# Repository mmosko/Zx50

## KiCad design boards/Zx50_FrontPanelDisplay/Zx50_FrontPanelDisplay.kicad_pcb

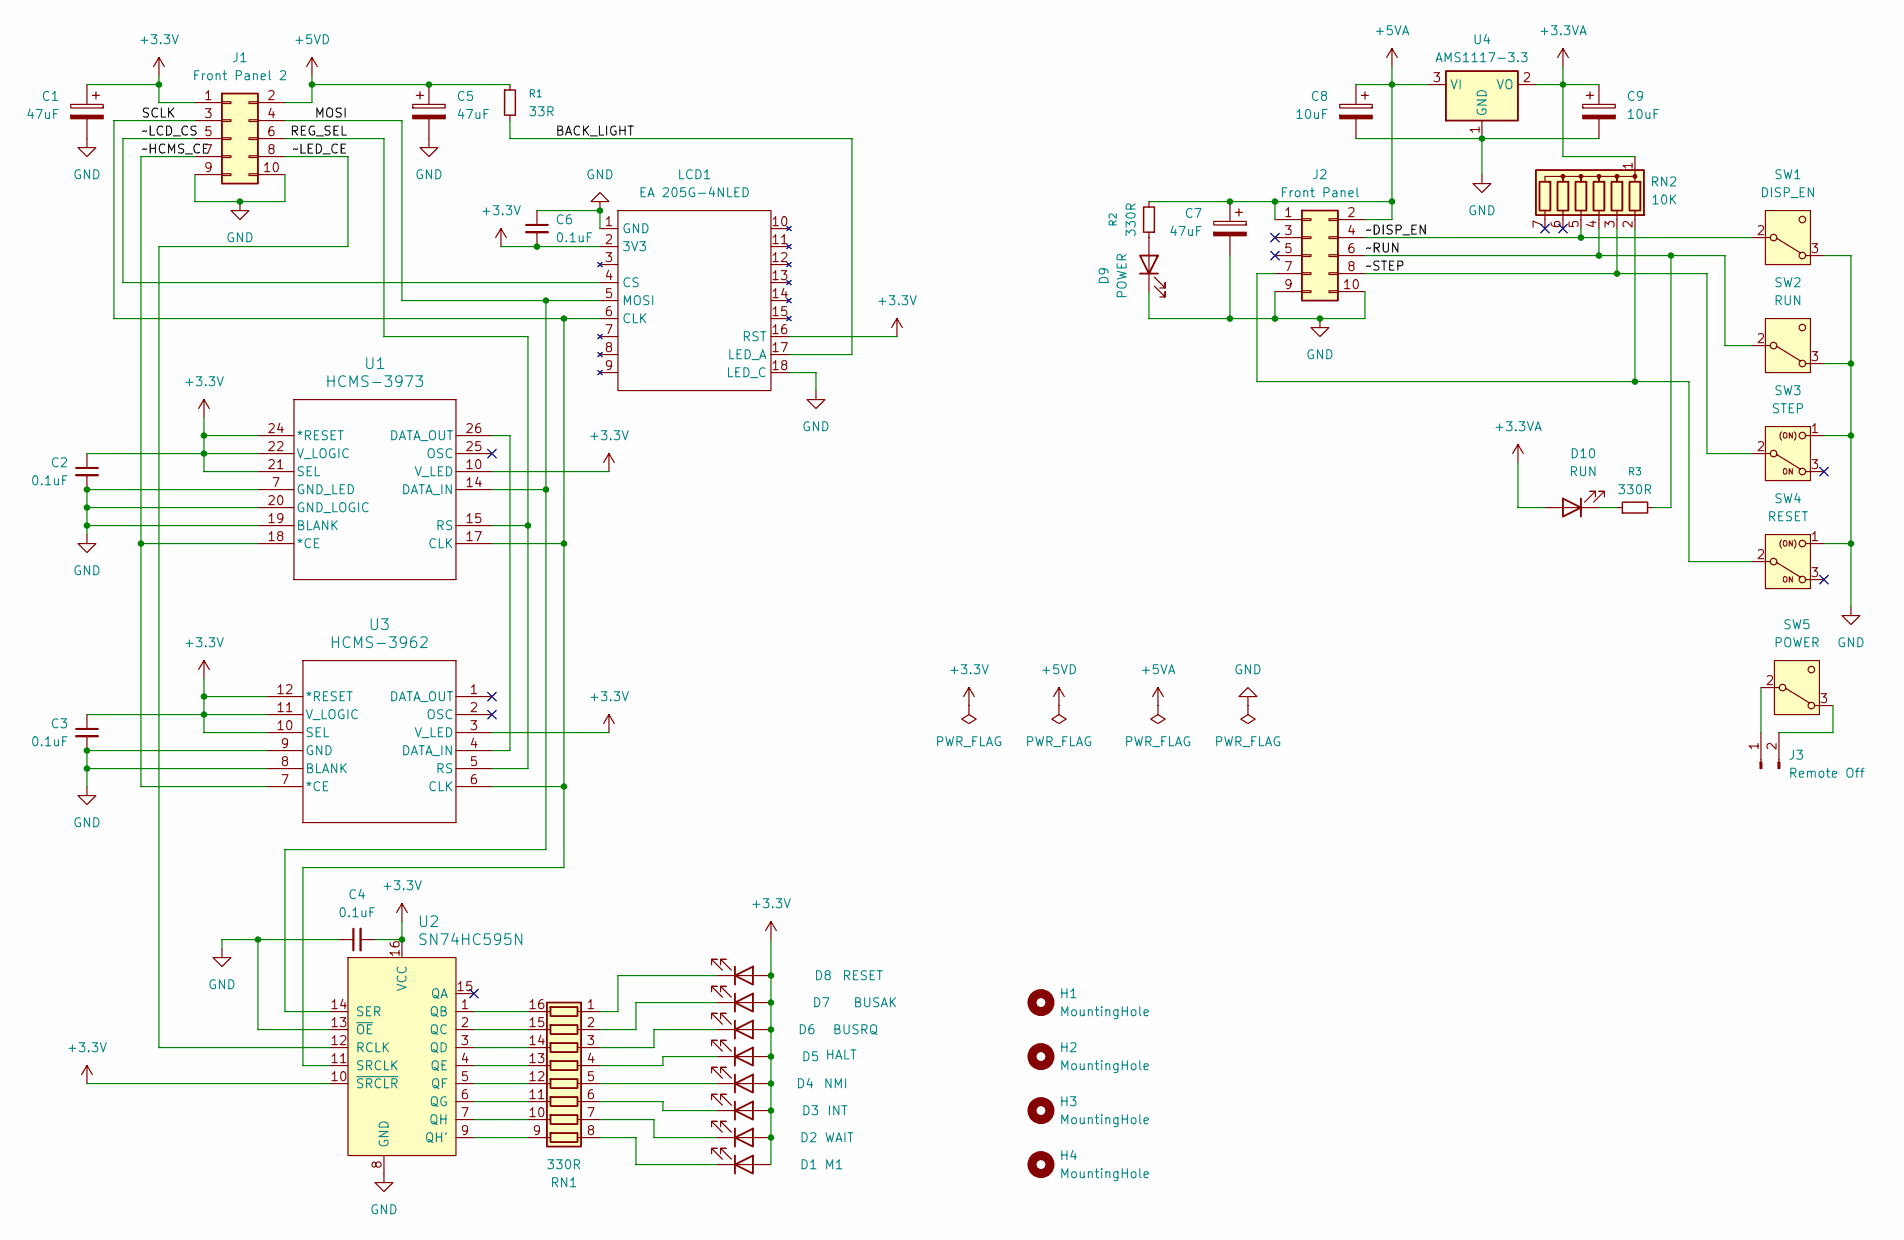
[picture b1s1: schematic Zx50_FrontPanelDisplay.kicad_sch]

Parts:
C1, C5, C7: 47uF; CP_Radial_D5.0mm_P2.00mm
C2, C3, C4, C6: 0.1uF; C_Disc_D5.0mm_W2.5mm_P5.00mm; DigiKey_PN BC1101CT-ND
C8, C9: 10uF; CP_Radial_Tantal_D5.0mm_P2.50mm; Mouser_PN 80-T350E106K025; DigiKey_PN 399-1418-ND
D1: M1; LED_D3.0mm
D2: WAIT; LED_D3.0mm
D3: INT; LED_D3.0mm
D4: NMI; LED_D3.0mm
D5: HALT; LED_D3.0mm
D6: BUSRQ; LED_D3.0mm
D7: BUSAK; LED_D3.0mm
D8: RESET; LED_D3.0mm
D9: POWER; LED_D3.0mm
D10: RUN; LED_D3.0mm
H1, H2, H3, H4: MountingHole; MountingHole_3.2mm_M3
J1: Front Panel 2; IDC-Header_2x05_P2.54mm_Vertical_SMD; Mouser_PN 710-61231020621; DigiKey_PN 732-2098-ND
J2: Front Panel; IDC-Header_2x05_P2.54mm_Vertical_SMD; Mouser_PN 710-61231020621; DigiKey_PN 732-2098-ND
J3: Remote Off; PinHeader_1x02_P2.54mm_Vertical
LCD1: EA 205G-4NLED; EA_DIG205G-4NLED; Digi-Key_PN 1481-EADIP205G-4NLED-ND
R1: 33R; R_Axial_DIN0207_L6.3mm_D2.5mm_P7.62mm_Horizontal
R2, R3: 330R; R_Axial_DIN0207_L6.3mm_D2.5mm_P7.62mm_Horizontal
RN1: 330R; DIP-16_W7.62mm
RN2: 10K; R_Array_SIP7
SW1: DISP_EN; NKK_MN11_SPST_W03
SW2: RUN; NKK_MN11_SPST_W03
SW3: STEP; NKK_MN15_SPDT_W03
SW4: RESET; NKK_MN15_SPDT_W03
SW5: POWER; NKK_MN11_SPST_W03
U1: HCMS-3973; DIP12_HCMS-397X_BRA
U2: SN74HC595N; SOP-16_4.4x10.4mm_P1.27mm; MPN SN74HC595N; Digi-Key_PN 296-1600-5-ND
U3: HCMS-3962; DIP12_HCMS-396X_BRA
U4: AMS1117-3.3; SOT-223-3_TabPin2; Mouser_PN 926-LM1117MPX3.3NOPB

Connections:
+3.3V: C1.1, C2.1, C3.1, C4.2, C6.2, D1.2 (A), D2.2 (A), D3.2 (A), D4.2 (A), D5.2 (A), D6.2 (A), D7.2 (A), D8.2 (A), J1.1, LCD1.2 (3V3), LCD1.16 (RST), U1.10 (V_LED), U1.21 (SEL), U1.22 (V_LOGIC), U1.24 (*RESET), U2.10 (~SRCLR), U2.16 (VCC), U3.3 (V_LED), U3.10 (SEL), U3.11 (V_LOGIC), U3.12 (*RESET)
+3.3VA: C9.1, D10.2 (A), RN2.1 (common), U4.2 (VO)
+5VA: C7.1, C8.1, J2.1, J2.2, R2.2, U4.3 (VI)
+5VD: C5.1, J1.2, R1.1
/BACK_LIGHT: LCD1.17 (LED_A), R1.2
/MOSI: J1.4, LCD1.5 (MOSI), U1.14 (DATA_IN), U2.14 (SER)
/REG_SEL: J1.6, U1.15 (RS), U3.5 (RS)
/SCLK: J1.3, LCD1.6 (CLK), U1.17 (CLK), U2.11 (SRCLK), U3.6 (CLK)
/~DISP_EN: J2.4, RN2.5 (R4), SW1.2 (B)
/~HCMS_CE: J1.7, U1.18 (*CE), U3.7 (*CE)
/~LCD_CS: J1.5, LCD1.4 (CS)
/~LED_CE: J1.8, U2.12 (RCLK)
/~RUN: J2.6, R3.2, RN2.4 (R3), SW2.2 (B)
/~STEP: J2.8, RN2.3 (R2), SW3.2 (B)
GND: C1.2, C2.2, C3.2, C4.1, C5.2, C6.1, C7.2, C8.2, C9.2, D9.1 (K), J1.9, J1.10, J2.9, J2.10, LCD1.1 (GND), LCD1.18 (LED_C), SW1.3 (C), SW2.3 (C), SW3.1 (A), SW4.1 (A), U1.7 (GND_LED), U1.19 (BLANK), U1.20 (GND_LOGIC), U2.8 (GND), U2.13 (~OE), U3.8 (BLANK), U3.9 (GND), U4.1 (GND)
unnamed: D1.1 (K), RN1.8 (R8.1)
unnamed: D2.1 (K), RN1.7 (R7.1)
unnamed: D3.1 (K), RN1.6 (R6.1)
unnamed: D4.1 (K), RN1.5 (R5.1)
unnamed: D5.1 (K), RN1.4 (R4.1)
unnamed: D6.1 (K), RN1.3 (R3.1)
unnamed: D7.1 (K), RN1.2 (R2.1)
unnamed: D8.1 (K), RN1.1 (R1.1)
unnamed: D9.2 (A), R2.1
unnamed: D10.1 (K), R3.1
unnamed: J2.7, RN2.2 (R1), SW4.2 (B)
unnamed: J3.1, SW5.2 (B)
unnamed: J3.2, SW5.3 (C)
unnamed: RN1.16 (R1.2), U2.1 (QB)
unnamed: RN1.15 (R2.2), U2.2 (QC)
unnamed: RN1.14 (R3.2), U2.3 (QD)
unnamed: RN1.13 (R4.2), U2.4 (QE)
unnamed: RN1.12 (R5.2), U2.5 (QF)
unnamed: RN1.11 (R6.2), U2.6 (QG)
unnamed: RN1.10 (R7.2), U2.7 (QH)
unnamed: RN1.9 (R8.2), U2.9 (QH')
unnamed: U1.26 (DATA_OUT), U3.4 (DATA_IN)

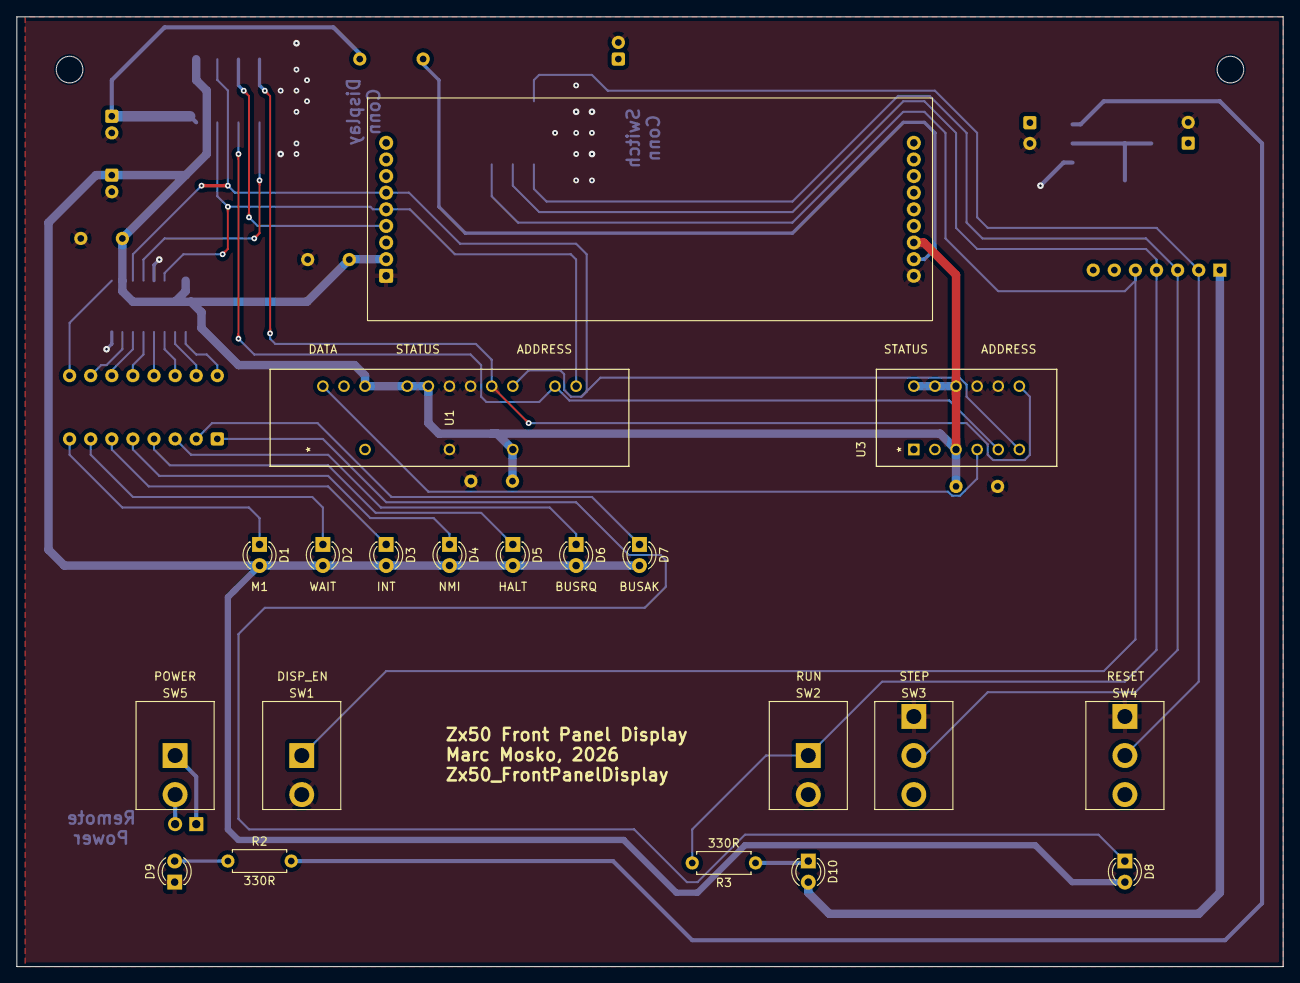
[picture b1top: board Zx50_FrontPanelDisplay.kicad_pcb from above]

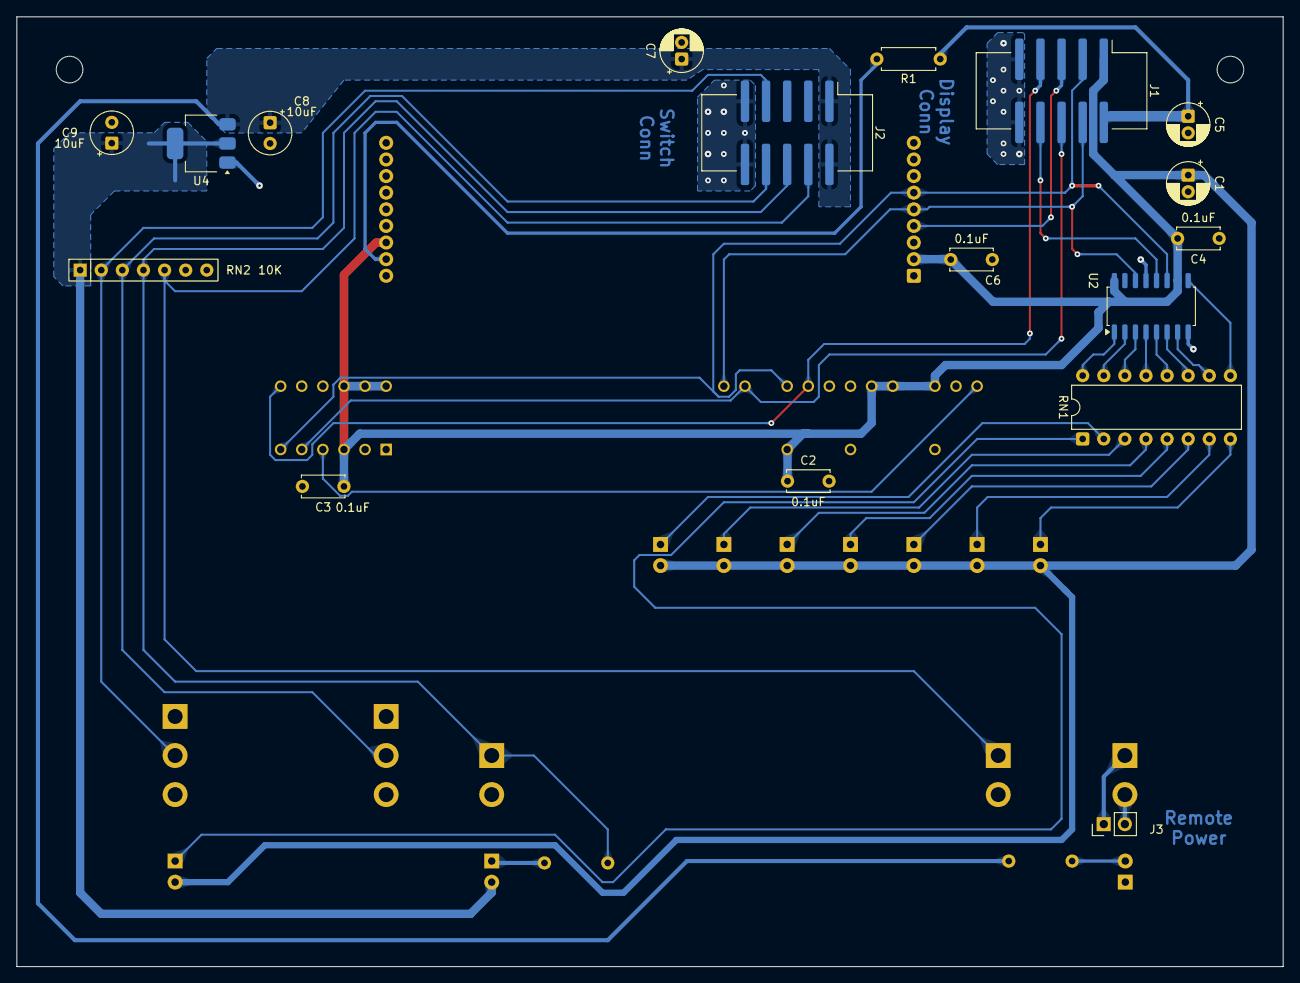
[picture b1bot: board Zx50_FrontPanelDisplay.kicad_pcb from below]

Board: 2 copper layers, 152.4 x 114.3 mm, 39 parts (17 on the bottom side), 37 nets.

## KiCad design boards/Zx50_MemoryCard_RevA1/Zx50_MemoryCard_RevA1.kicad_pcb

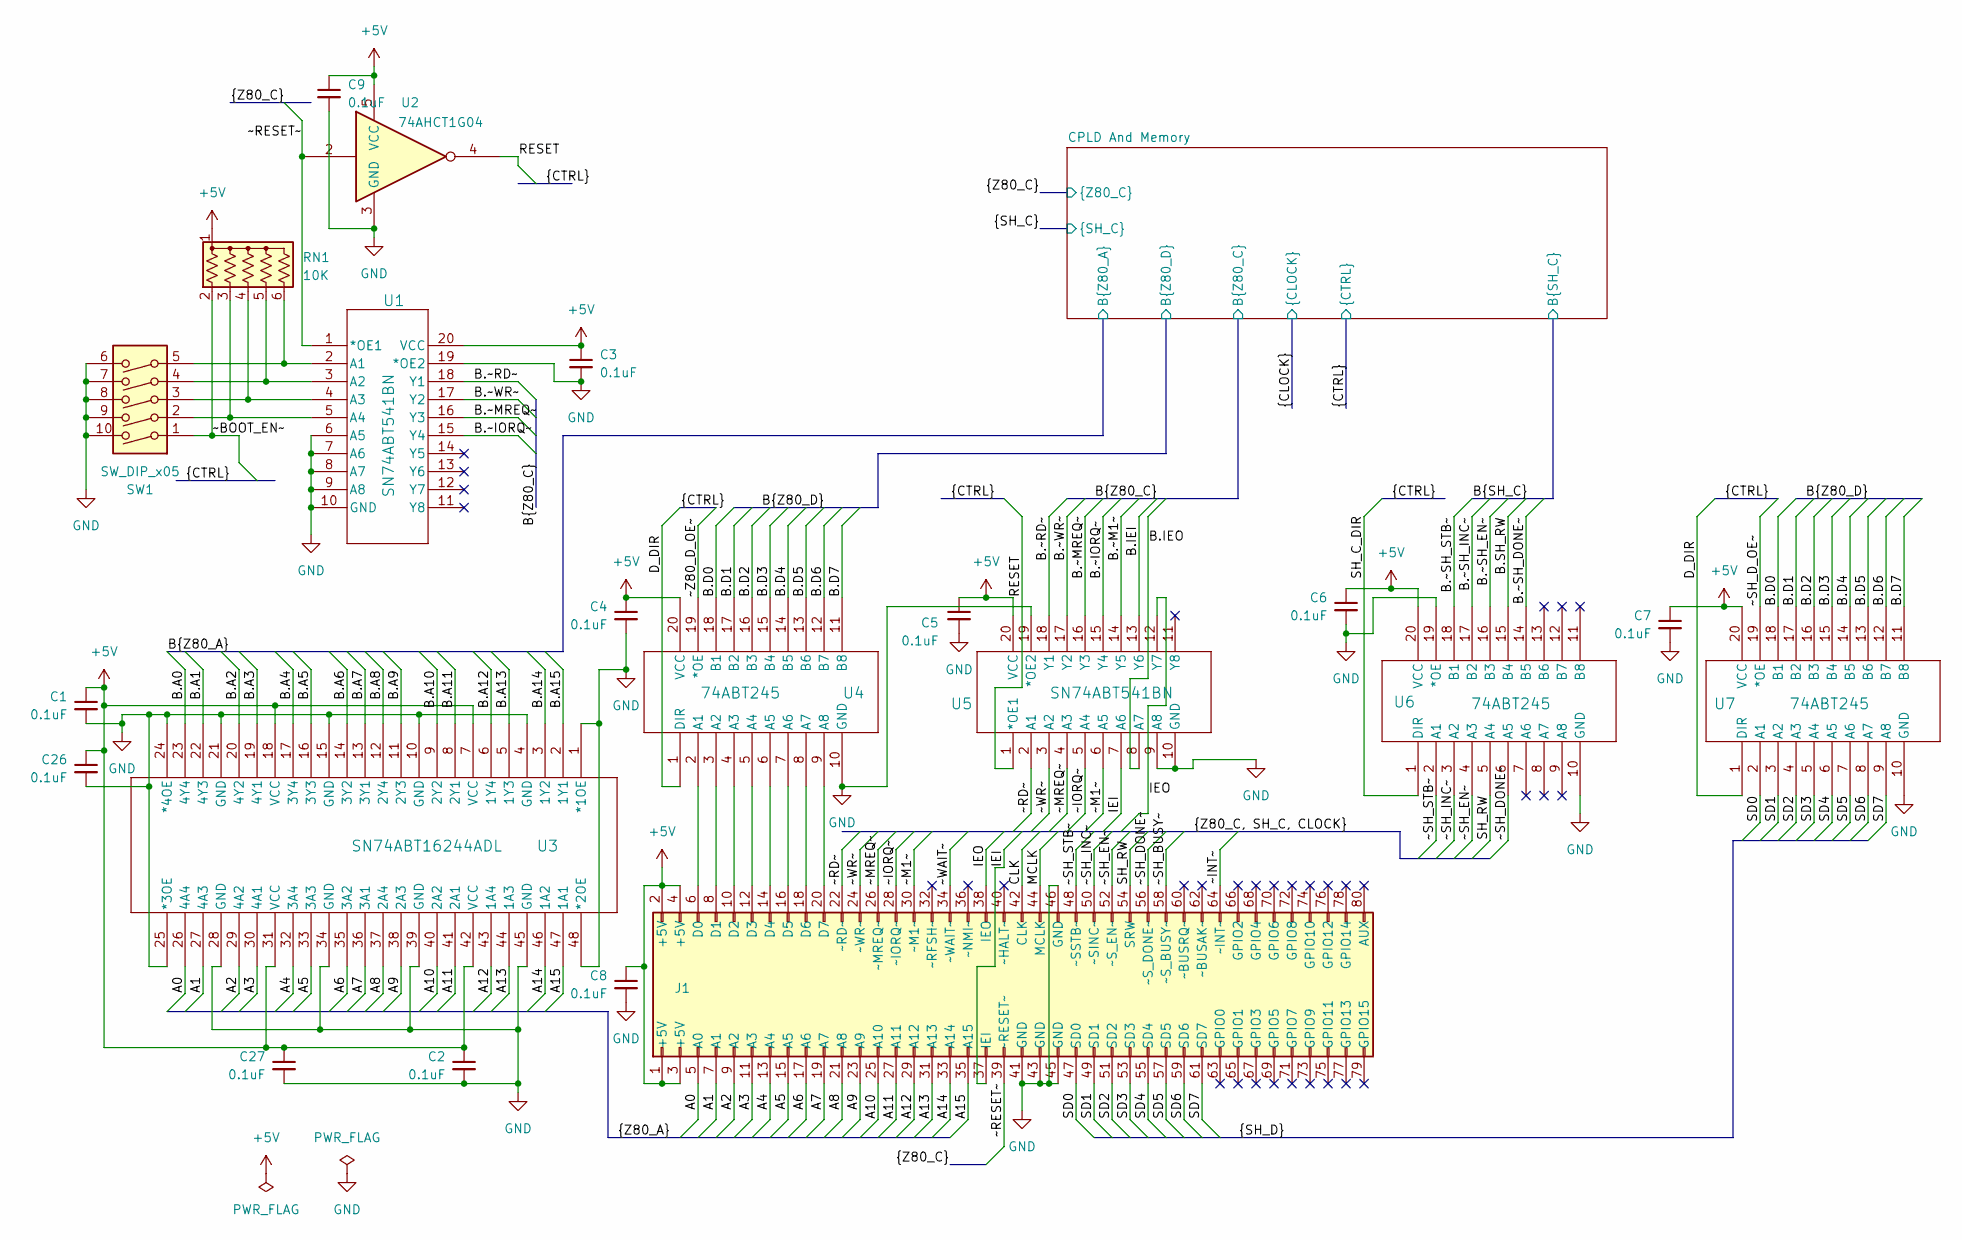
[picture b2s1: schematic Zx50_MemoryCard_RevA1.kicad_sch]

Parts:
C1, C2, C3, C4, C5, C6, C7, C8, C9, C26, C27: 0.1uF; C_0603_1608Metric; LCSC C14663
J1: Zx50_EdgeConnector; PinSocket_2x40_P2.54mm_Horizontal_Edge; DigiKey_PN 2057-PH2RA-80-UA-ND
RN1: 10K; R_Array_SIP6; LCSC 4606X-AP1-103LF
SW1: SW_DIP_x05; SW_DIP_SPSTx05_Slide_9.78x14.88mm_W7.62mm_P2.54mm; LCSC 208-5
U1, U5: SN74ABT541BN; TSSOP-20_4.4x6.5mm_P0.65mm; LCSC C131956
U2: 74AHCT1G04; SOT-23-5; LCSC C52140419
U3: SN74ABT16244ADL; SSOP-48_7.5x15.9mm_P0.635mm; LCSC C2869608
U4, U6, U7: 74ABT245; SOIC-20W_7.5x12.8mm_P1.27mm; LCSC C1548132

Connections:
+5V: C1.1, C2.1, C3.1, C4.1, C5.1, C6.1, C7.1, C8.1, C9.1, C26.1, C27.1, J1.1 (+5V), J1.2 (+5V), J1.3 (+5V), J1.4 (+5V), RN1.1 (common), U1.20 (VCC), U2.5 (VCC), U3.7 (VCC), U3.18 (VCC), U3.31 (VCC), U3.42 (VCC), U4.20 (VCC), U5.20 (VCC), U6.20 (VCC), U7.20 (VCC); also elsewhere on the board
/A0: J1.5 (A0), U3.26 (4A4)
/A1: J1.7 (A1), U3.27 (4A3)
/A2: J1.9 (A2), U3.29 (4A2)
/A3: J1.11 (A3), U3.30 (4A1)
/A4: J1.13 (A4), U3.32 (3A4)
/A5: J1.15 (A5), U3.33 (3A3)
/A6: J1.17 (A6), U3.35 (3A2)
/A7: J1.19 (A7), U3.36 (3A1)
/A8: J1.21 (A8), U3.37 (2A4)
/A9: J1.23 (A9), U3.38 (2A3)
/A10: J1.25 (A10), U3.40 (2A2)
/A11: J1.27 (A11), U3.41 (2A1)
/A12: J1.29 (A12), U3.43 (1A4)
/A13: J1.31 (A13), U3.44 (1A3)
/A14: J1.33 (A14), U3.46 (1A2)
/A15: J1.35 (A15), U3.47 (1A1)
/B.A0: U3.23 (4Y4); also elsewhere on the board
/B.A1: U3.22 (4Y3); also elsewhere on the board
/B.A2: U3.20 (4Y2); also elsewhere on the board
/B.A3: U3.19 (4Y1); also elsewhere on the board
/B.A4: U3.17 (3Y4); also elsewhere on the board
/B.A5: U3.16 (3Y3); also elsewhere on the board
/B.A6: U3.14 (3Y2); also elsewhere on the board
/B.A7: U3.13 (3Y1); also elsewhere on the board
/B.A8: U3.12 (2Y4); also elsewhere on the board
/B.A9: U3.11 (2Y3); also elsewhere on the board
/B.A10: U3.9 (2Y2); also elsewhere on the board
/B.A11: U3.8 (2Y1); also elsewhere on the board
/B.A12: U3.6 (1Y4); also elsewhere on the board
/B.A13: U3.5 (1Y3); also elsewhere on the board
/B.A14: U3.3 (1Y2); also elsewhere on the board
/B.A15: U3.2 (1Y1); also elsewhere on the board
/B.D0: U4.18 (B1), U7.18 (B1); also elsewhere on the board
/B.D1: U4.17 (B2), U7.17 (B2); also elsewhere on the board
/B.D2: U4.16 (B3), U7.16 (B3); also elsewhere on the board
/B.D3: U4.15 (B4), U7.15 (B4); also elsewhere on the board
/B.D4: U4.14 (B5), U7.14 (B5); also elsewhere on the board
/B.D5: U4.13 (B6), U7.13 (B6); also elsewhere on the board
/B.D6: U4.12 (B7), U7.12 (B7); also elsewhere on the board
/B.D7: U4.11 (B8), U7.11 (B8); also elsewhere on the board
/B.IEI: U5.13 (Y6); also elsewhere on the board
/B.IEO: U5.8 (A7); also elsewhere on the board
/B.SH_RW: U6.15 (B4); also elsewhere on the board
/B.~IORQ~: U1.15 (Y4), U5.15 (Y4); also elsewhere on the board
/B.~M1~: U5.14 (Y5); also elsewhere on the board
/B.~MREQ~: U1.16 (Y3), U5.16 (Y3); also elsewhere on the board
/B.~RD~: U1.18 (Y1), U5.18 (Y1); also elsewhere on the board
/B.~SH_DONE~: U6.14 (B5); also elsewhere on the board
/B.~SH_EN~: U6.16 (B3); also elsewhere on the board
/B.~SH_INC~: U6.17 (B2); also elsewhere on the board
/B.~SH_STB~: U6.18 (B1); also elsewhere on the board
/B.~WR~: U1.17 (Y2), U5.17 (Y2); also elsewhere on the board
/CLK: J1.42 (CLK); also elsewhere on the board
/D_DIR: U4.1 (DIR), U7.1 (DIR); also elsewhere on the board
/IEI: J1.37 (IEI), U5.7 (A6)
/IEO: J1.38 (IEO), U5.12 (Y7)
/MCLK: J1.44 (MCLK); also elsewhere on the board
/RESET: U2.4, U5.1 (*OE1)
/SD0: J1.47 (SD0), U7.2 (A1)
/SD1: J1.49 (SD1), U7.3 (A2)
/SD2: J1.51 (SD2), U7.4 (A3)
/SD3: J1.53 (SD3), U7.5 (A4)
/SD4: J1.55 (SD4), U7.6 (A5)
/SD5: J1.57 (SD5), U7.7 (A6)
/SD6: J1.59 (SD6), U7.8 (A7)
/SD7: J1.61 (SD7), U7.9 (A8)
/SH_C_DIR: U6.1 (DIR); also elsewhere on the board
/SH_RW: J1.54 (SRW), U6.5 (A4)
/~BOOT_EN~: RN1.2 (R1), SW1.1; also elsewhere on the board
/~INT~: J1.64 (~INT~); also elsewhere on the board
/~IORQ~: J1.28 (~IORQ~), U5.5 (A4)
/~M1~: J1.30 (~M1~), U5.6 (A5)
/~MREQ~: J1.26 (~MREQ~), U5.4 (A3)
/~RD~: J1.22 (~RD~), U5.2 (A1)
/~RESET~: J1.39 (~RESET~), U1.1 (*OE1), U2.2; also elsewhere on the board
/~SH_BUSY~: J1.58 (~S_BUSY~); also elsewhere on the board
/~SH_DONE~: J1.56 (~S_DONE~), U6.6 (A5)
/~SH_D_OE~: U7.19 (*OE); also elsewhere on the board
/~SH_EN~: J1.52 (~S_EN~), U6.4 (A3)
/~SH_INC~: J1.50 (~SINC~), U6.3 (A2)
/~SH_STB~: J1.48 (~SSTB~), U6.2 (A1)
/~WAIT~: J1.34 (~WAIT~); also elsewhere on the board
/~WR~: J1.24 (~WR~), U5.3 (A2)
/~Z80_D_OE~: U4.19 (*OE); also elsewhere on the board
GND: C1.2, C2.2, C3.2, C4.2, C5.2, C6.2, C7.2, C8.2, C9.2, C26.2, C27.2, J1.41 (GND), J1.43 (GND), J1.45 (GND), J1.46 (GND), SW1.6, SW1.7, SW1.8, SW1.9, SW1.10, U1.6 (A5), U1.7 (A6), U1.8 (A7), U1.9 (A8), U1.10 (GND), U1.19 (*OE2), U2.3 (GND), U3.1 (*1OE), U3.4 (GND), U3.10 (GND), U3.15 (GND), U3.21 (GND), U3.24 (*4OE), U3.25 (*3OE), U3.28 (GND), U3.34 (GND), U3.39 (GND), U3.45 (GND), U3.48 (*2OE), U4.10 (GND), U5.9 (A8), U5.10 (GND), U5.19 (*OE2), U6.10 (GND), U6.19 (*OE), U7.10 (GND); also elsewhere on the board
unnamed: J1.6 (D0), U4.2 (A1)
unnamed: J1.8 (D1), U4.3 (A2)
unnamed: J1.10 (D2), U4.4 (A3)
unnamed: J1.12 (D3), U4.5 (A4)
unnamed: J1.14 (D4), U4.6 (A5)
unnamed: J1.16 (D5), U4.7 (A6)
unnamed: J1.18 (D6), U4.8 (A7)
unnamed: J1.20 (D7), U4.9 (A8)
unnamed: RN1.3 (R2), SW1.2, U1.5 (A4)
unnamed: RN1.4 (R3), SW1.3, U1.4 (A3)
unnamed: RN1.5 (R4), SW1.4, U1.3 (A2)
unnamed: RN1.6 (R5), SW1.5, U1.2 (A1)

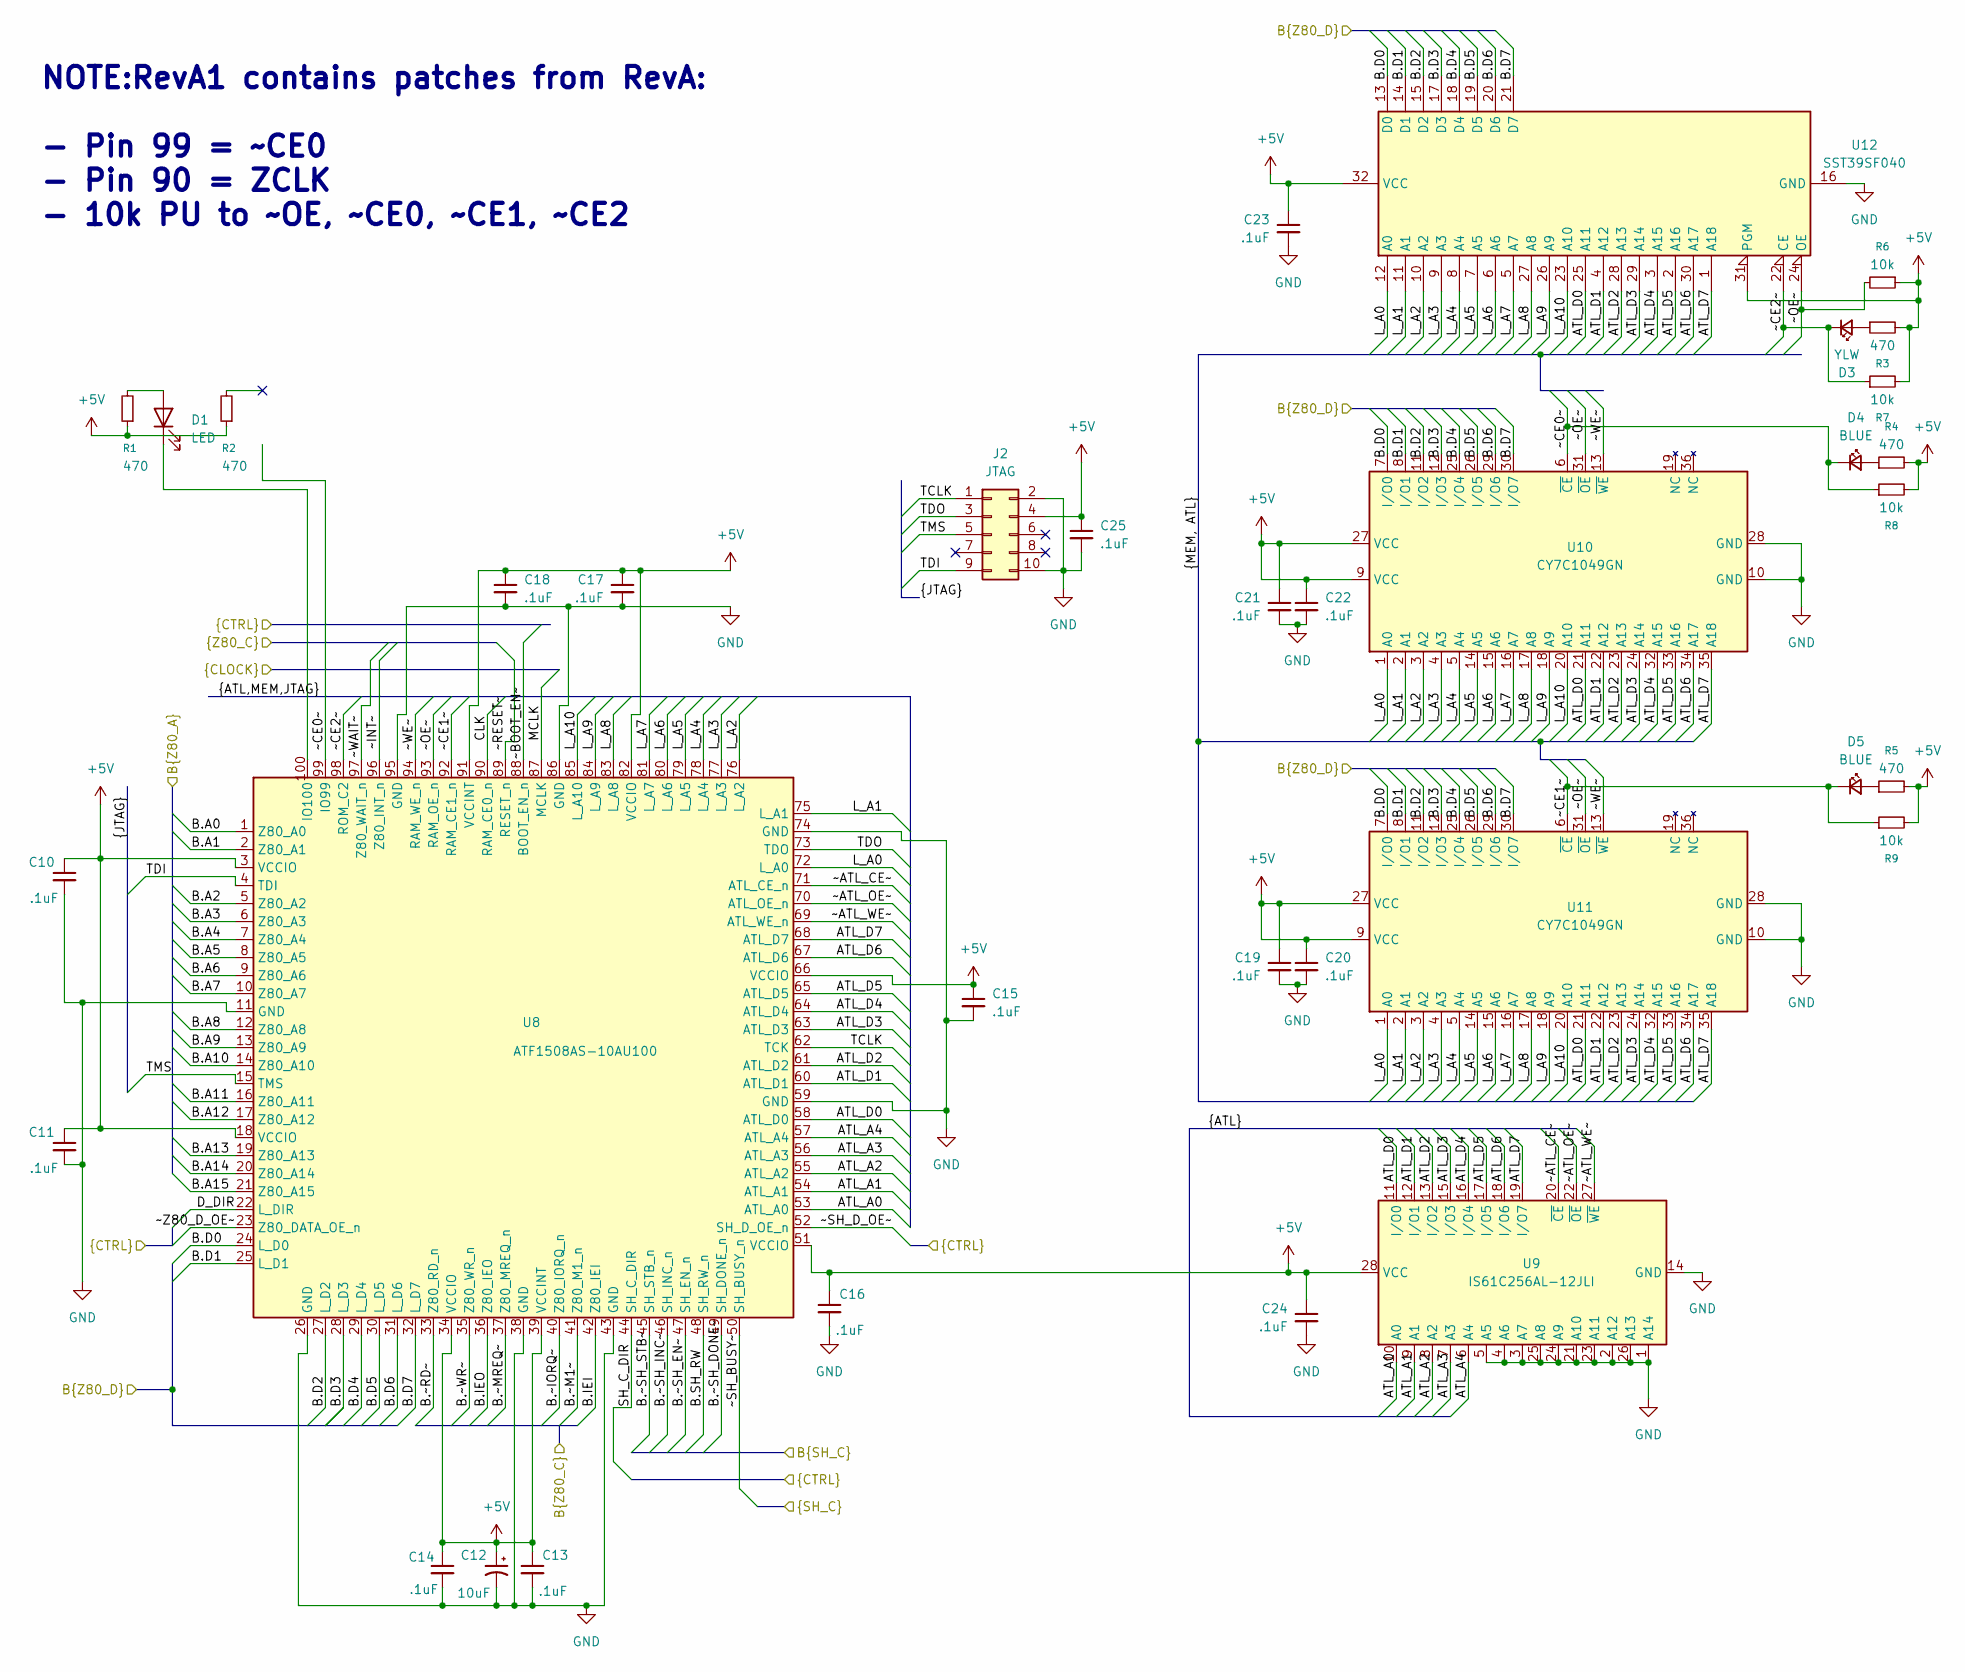
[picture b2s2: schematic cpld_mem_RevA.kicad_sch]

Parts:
C10, C11, C13, C14, C15, C16, C17, C18, C19, C20, C21, C22, C23, C24, C25: .1uF; C_0603_1608Metric; LCSC C14663
C12: 10uF; CP_Radial_Tantal_D5.0mm_P2.50mm
D1: LED; LED_D3.0mm_Horizontal_O1.27mm_Z2.0mm
D3: YLW; LED_0805_2012Metric; LCSC C2296
D4, D5: BLUE; LED_0805_2012Metric; LCSC C2293
J2: JTAG; IDC-Header_2x05_P2.54mm_Vertical; DigiKey_PN 732-2094-ND
R1, R2: 470; R_Axial_DIN0207_L6.3mm_D2.5mm_P7.62mm_Horizontal
R3, R4, R5: 470; R_0805_2012Metric; LCSC C17710
R6, R7, R8, R9: 10k
U8: ATF1508AS-10AU100; TQFP-100_14x14mm_P0.5mm; LCSC C31179
U9: IS61C256AL-12JLI; SOJ-28_7.62x18.415mm_P1.27mm; LCSC C2062861
U10, U11: CY7C1049GN; SOJ-36_10.16x23.495mm_P1.27mm; LCSC C2955765
U12: SST39SF040; DIP-32_W15.24mm_Socket; DigiKey_PN SST39SF040-70-4C-PHE-ND

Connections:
+5V: C10.1, C11.1, C12.1, C13.1, C14.1, C15.1, C16.1, C17.1, C18.1, C19.1, C20.1, C21.1, C22.1, C23.1, C24.1, C25.1, J2.4, R1.1, R2.1, R3.2, R4.2, R5.2, R6.1, R7.2, R8.2, R9.2, U8.3 (VCCIO), U8.18 (VCCIO), U8.34 (VCCIO), U8.39 (VCCINT), U8.51 (VCCIO), U8.66 (VCCIO), U8.82 (VCCIO), U8.91 (VCCINT), U9.28 (VCC), U10.9 (VCC), U10.27 (VCC), U11.9 (VCC), U11.27 (VCC), U12.31 (PGM), U12.32 (VCC); also elsewhere on the board
/B.A0: U8.1 (Z80_A0); also elsewhere on the board
/B.A1: U8.2 (Z80_A1); also elsewhere on the board
/B.A2: U8.5 (Z80_A2); also elsewhere on the board
/B.A3: U8.6 (Z80_A3); also elsewhere on the board
/B.A4: U8.7 (Z80_A4); also elsewhere on the board
/B.A5: U8.8 (Z80_A5); also elsewhere on the board
/B.A6: U8.9 (Z80_A6); also elsewhere on the board
/B.A7: U8.10 (Z80_A7); also elsewhere on the board
/B.A8: U8.12 (Z80_A8); also elsewhere on the board
/B.A9: U8.13 (Z80_A9); also elsewhere on the board
/B.A10: U8.14 (Z80_A10); also elsewhere on the board
/B.A11: U8.16 (Z80_A11); also elsewhere on the board
/B.A12: U8.17 (Z80_A12); also elsewhere on the board
/B.A13: U8.19 (Z80_A13); also elsewhere on the board
/B.A14: U8.20 (Z80_A14); also elsewhere on the board
/B.A15: U8.21 (Z80_A15); also elsewhere on the board
/B.D0: U8.24 (L_D0), U10.7 (I/O0), U11.7 (I/O0), U12.13 (D0); also elsewhere on the board
/B.D1: U8.25 (L_D1), U10.8 (I/O1), U11.8 (I/O1), U12.14 (D1); also elsewhere on the board
/B.D2: U8.27 (L_D2), U10.11 (I/O2), U11.11 (I/O2), U12.15 (D2); also elsewhere on the board
/B.D3: U8.28 (L_D3), U10.12 (I/O3), U11.12 (I/O3), U12.17 (D3); also elsewhere on the board
/B.D4: U8.29 (L_D4), U10.25 (I/O4), U11.25 (I/O4), U12.18 (D4); also elsewhere on the board
/B.D5: U8.30 (L_D5), U10.26 (I/O5), U11.26 (I/O5), U12.19 (D5); also elsewhere on the board
/B.D6: U8.31 (L_D6), U10.29 (I/O6), U11.29 (I/O6), U12.20 (D6); also elsewhere on the board
/B.D7: U8.32 (L_D7), U10.30 (I/O7), U11.30 (I/O7), U12.21 (D7); also elsewhere on the board
/B.IEI: U8.42 (Z80_IEI); also elsewhere on the board
/B.IEO: U8.36 (Z80_IEO); also elsewhere on the board
/B.SH_RW: U8.48 (SH_RW_n); also elsewhere on the board
/B.~IORQ~: U8.40 (Z80_IORQ_n); also elsewhere on the board
/B.~M1~: U8.41 (Z80_M1_n); also elsewhere on the board
/B.~MREQ~: U8.37 (Z80_MREQ_n); also elsewhere on the board
/B.~RD~: U8.33 (Z80_RD_n); also elsewhere on the board
/B.~SH_DONE~: U8.49 (SH_DONE_n); also elsewhere on the board
/B.~SH_EN~: U8.47 (SH_EN_n); also elsewhere on the board
/B.~SH_INC~: U8.46 (SH_INC_n); also elsewhere on the board
/B.~SH_STB~: U8.45 (SH_STB_n); also elsewhere on the board
/B.~WR~: U8.35 (Z80_WR_n); also elsewhere on the board
/CLK: U8.90 (RAM_CE0_n); also elsewhere on the board
/CPLD And Memory/ATL_A0: U8.53 (ATL_A0), U9.10 (A0)
/CPLD And Memory/ATL_A1: U8.54 (ATL_A1), U9.9 (A1)
/CPLD And Memory/ATL_A2: U8.55 (ATL_A2), U9.8 (A2)
/CPLD And Memory/ATL_A3: U8.56 (ATL_A3), U9.7 (A3)
/CPLD And Memory/ATL_A4: U8.57 (ATL_A4), U9.6 (A4)
/CPLD And Memory/ATL_D0: U8.58 (ATL_D0), U9.11 (I/O0), U10.21 (A11), U11.21 (A11), U12.25 (A11)
/CPLD And Memory/ATL_D1: U8.60 (ATL_D1), U9.12 (I/O1), U10.22 (A12), U11.22 (A12), U12.4 (A12)
/CPLD And Memory/ATL_D2: U8.61 (ATL_D2), U9.13 (I/O2), U10.23 (A13), U11.23 (A13), U12.28 (A13)
/CPLD And Memory/ATL_D3: U8.63 (ATL_D3), U9.15 (I/O3), U10.24 (A14), U11.24 (A14), U12.29 (A14)
/CPLD And Memory/ATL_D4: U8.64 (ATL_D4), U9.16 (I/O4), U10.32 (A15), U11.32 (A15), U12.3 (A15)
/CPLD And Memory/ATL_D5: U8.65 (ATL_D5), U9.17 (I/O5), U10.33 (A16), U11.33 (A16), U12.2 (A16)
/CPLD And Memory/ATL_D6: U8.67 (ATL_D6), U9.18 (I/O6), U10.34 (A17), U11.34 (A17), U12.30 (A17)
/CPLD And Memory/ATL_D7: U8.68 (ATL_D7), U9.19 (I/O7), U10.35 (A18), U11.35 (A18), U12.1 (A18)
/CPLD And Memory/L_A0: U8.72 (L_A0), U10.1 (A0), U11.1 (A0), U12.12 (A0)
/CPLD And Memory/L_A1: U8.75 (L_A1), U10.2 (A1), U11.2 (A1), U12.11 (A1)
/CPLD And Memory/L_A2: U8.76 (L_A2), U10.3 (A2), U11.3 (A2), U12.10 (A2)
/CPLD And Memory/L_A3: U8.77 (L_A3), U10.4 (A3), U11.4 (A3), U12.9 (A3)
/CPLD And Memory/L_A4: U8.78 (L_A4), U10.5 (A4), U11.5 (A4), U12.8 (A4)
/CPLD And Memory/L_A5: U8.79 (L_A5), U10.14 (A5), U11.14 (A5), U12.7 (A5)
/CPLD And Memory/L_A6: U8.80 (L_A6), U10.15 (A6), U11.15 (A6), U12.6 (A6)
/CPLD And Memory/L_A7: U8.81 (L_A7), U10.16 (A7), U11.16 (A7), U12.5 (A7)
/CPLD And Memory/L_A8: U8.83 (L_A8), U10.17 (A8), U11.17 (A8), U12.27 (A8)
/CPLD And Memory/L_A9: U8.84 (L_A9), U10.18 (A9), U11.18 (A9), U12.26 (A9)
/CPLD And Memory/L_A10: U8.85 (L_A10), U10.20 (A10), U11.20 (A10), U12.23 (A10)
/CPLD And Memory/TCLK: J2.1, U8.62 (TCK)
/CPLD And Memory/TDI: J2.9, U8.4 (TDI)
/CPLD And Memory/TDO: J2.3, U8.73 (TDO)
/CPLD And Memory/TMS: J2.5, U8.15 (TMS)
/CPLD And Memory/~ATL_CE~: U8.71 (ATL_CE_n), U9.20 (~CE)
/CPLD And Memory/~ATL_OE~: U8.70 (ATL_OE_n), U9.22 (~OE)
/CPLD And Memory/~ATL_WE~: U8.69 (ATL_WE_n), U9.27 (~WE)
/CPLD And Memory/~CE0~: D4.1 (K), R8.1, U8.99 (IO99), U10.6 (~CE)
/CPLD And Memory/~CE1~: D5.1 (K), R9.1, U8.92 (RAM_CE1_n), U11.6 (~CE)
/CPLD And Memory/~CE2~: D3.1 (K), R7.1, U8.98 (ROM_C2), U12.22 (CE)
/CPLD And Memory/~OE~: R6.2, U8.93 (RAM_OE_n), U10.31 (~OE), U11.31 (~OE), U12.24 (OE)
/CPLD And Memory/~WE~: U8.94 (RAM_WE_n), U10.13 (~WE), U11.13 (~WE)
/D_DIR: U8.22 (L_DIR); also elsewhere on the board
/MCLK: U8.87 (MCLK); also elsewhere on the board
/SH_C_DIR: U8.44 (SH_C_DIR); also elsewhere on the board
/~BOOT_EN~: U8.88 (BOOT_EN_n); also elsewhere on the board
/~INT~: U8.96 (Z80_INT_n); also elsewhere on the board
/~RESET~: U8.89 (RESET_n); also elsewhere on the board
/~SH_BUSY~: U8.50 (SH_BUSY_n); also elsewhere on the board
/~SH_D_OE~: U8.52 (SH_D_OE_n); also elsewhere on the board
/~WAIT~: U8.97 (Z80_WAIT_n); also elsewhere on the board
/~Z80_D_OE~: U8.23 (Z80_DATA_OE_n); also elsewhere on the board
GND: C10.2, C11.2, C12.2, C13.2, C14.2, C15.2, C16.2, C17.2, C18.2, C19.2, C20.2, C21.2, C22.2, C23.2, C24.2, C25.2, J2.2, J2.10, U8.11 (GND), U8.26 (GND), U8.38 (GND), U8.43 (GND), U8.59 (GND), U8.74 (GND), U8.86 (GND), U8.95 (GND), U9.1 (A14), U9.2 (A12), U9.3 (A7), U9.4 (A6), U9.5 (A5), U9.14 (GND), U9.21 (A10), U9.23 (A11), U9.24 (A9), U9.25 (A8), U9.26 (A13), U10.10 (GND), U10.28 (GND), U11.10 (GND), U11.28 (GND), U12.16 (GND); also elsewhere on the board
unnamed: D1.2 (A), R1.2
unnamed: D1.1 (K), U8.100 (IO100)
unnamed: D3.2 (A), R3.1
unnamed: D4.2 (A), R4.1
unnamed: D5.2 (A), R5.1

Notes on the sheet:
NOTE:RevA1 contains patches from RevA: - Pin 99 = ~CE0 - Pin 90 = ZCLK - 10k PU to ~OE, ~CE0, ~CE1, ~CE2

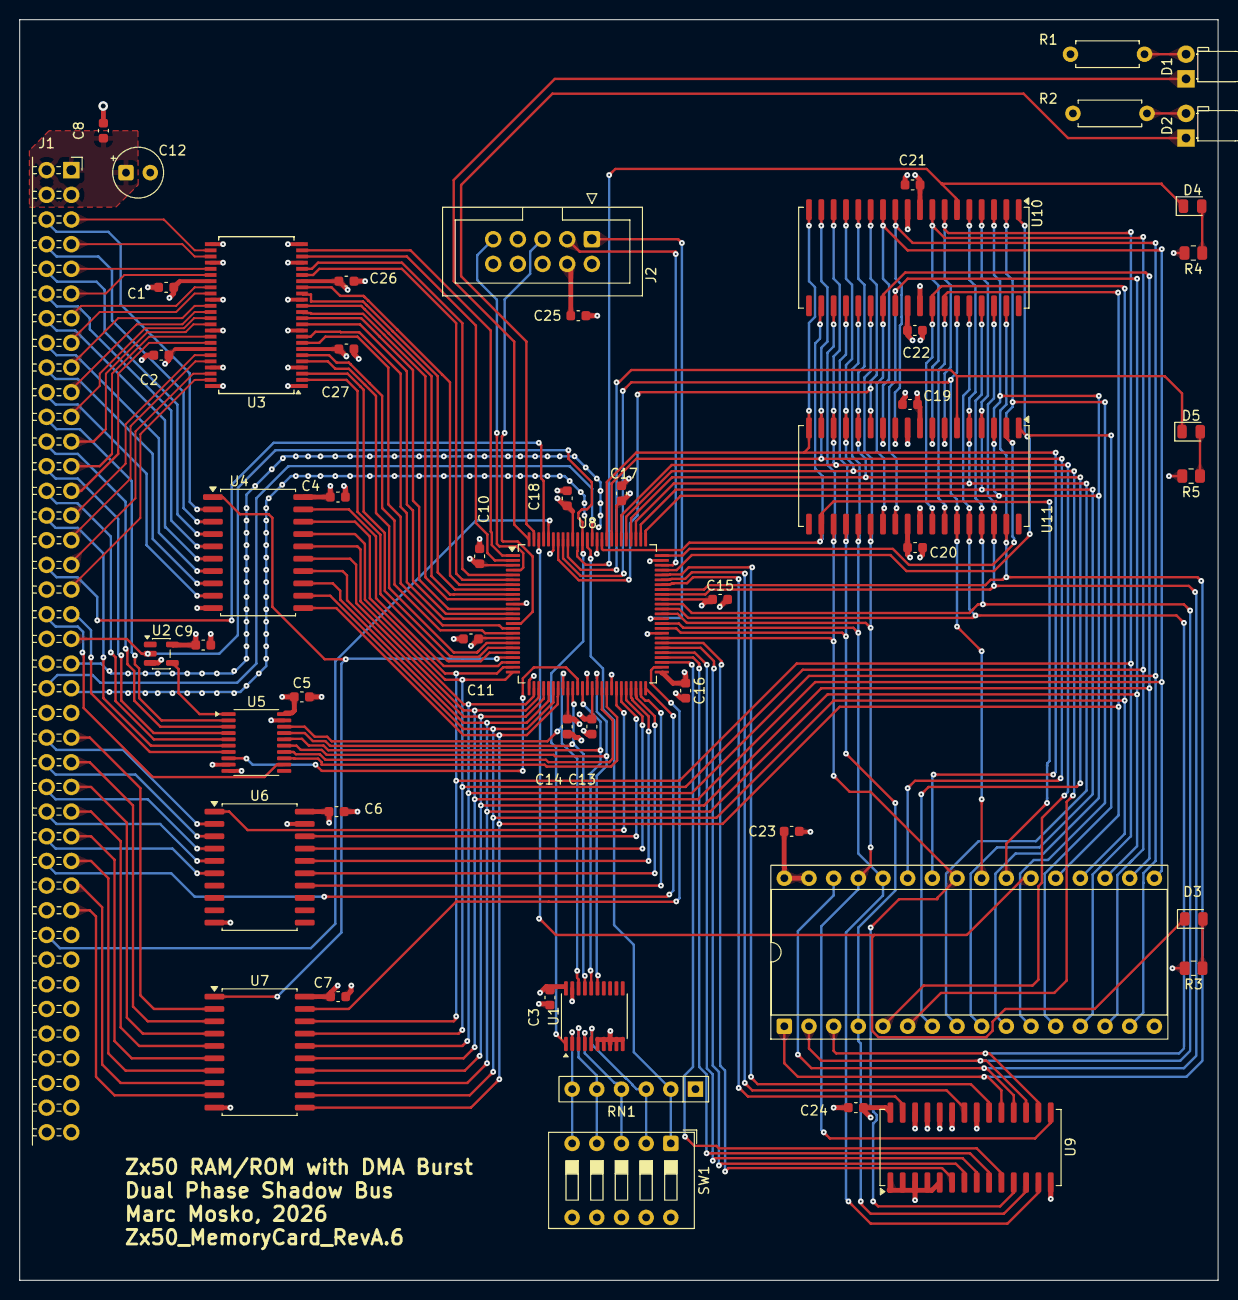
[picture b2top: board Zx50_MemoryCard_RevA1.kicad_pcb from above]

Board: 4 copper layers, 123.4 x 129.8 mm, 53 parts (0 on the bottom side), 139 nets.

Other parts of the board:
D2: LED; LED_D3.0mm_Horizontal_O1.27mm_Z2.0mm
